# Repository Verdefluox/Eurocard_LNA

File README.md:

# Eurocard_LNA
A general purpose AC/DC low noise preamplifier on Eurocard format PCB

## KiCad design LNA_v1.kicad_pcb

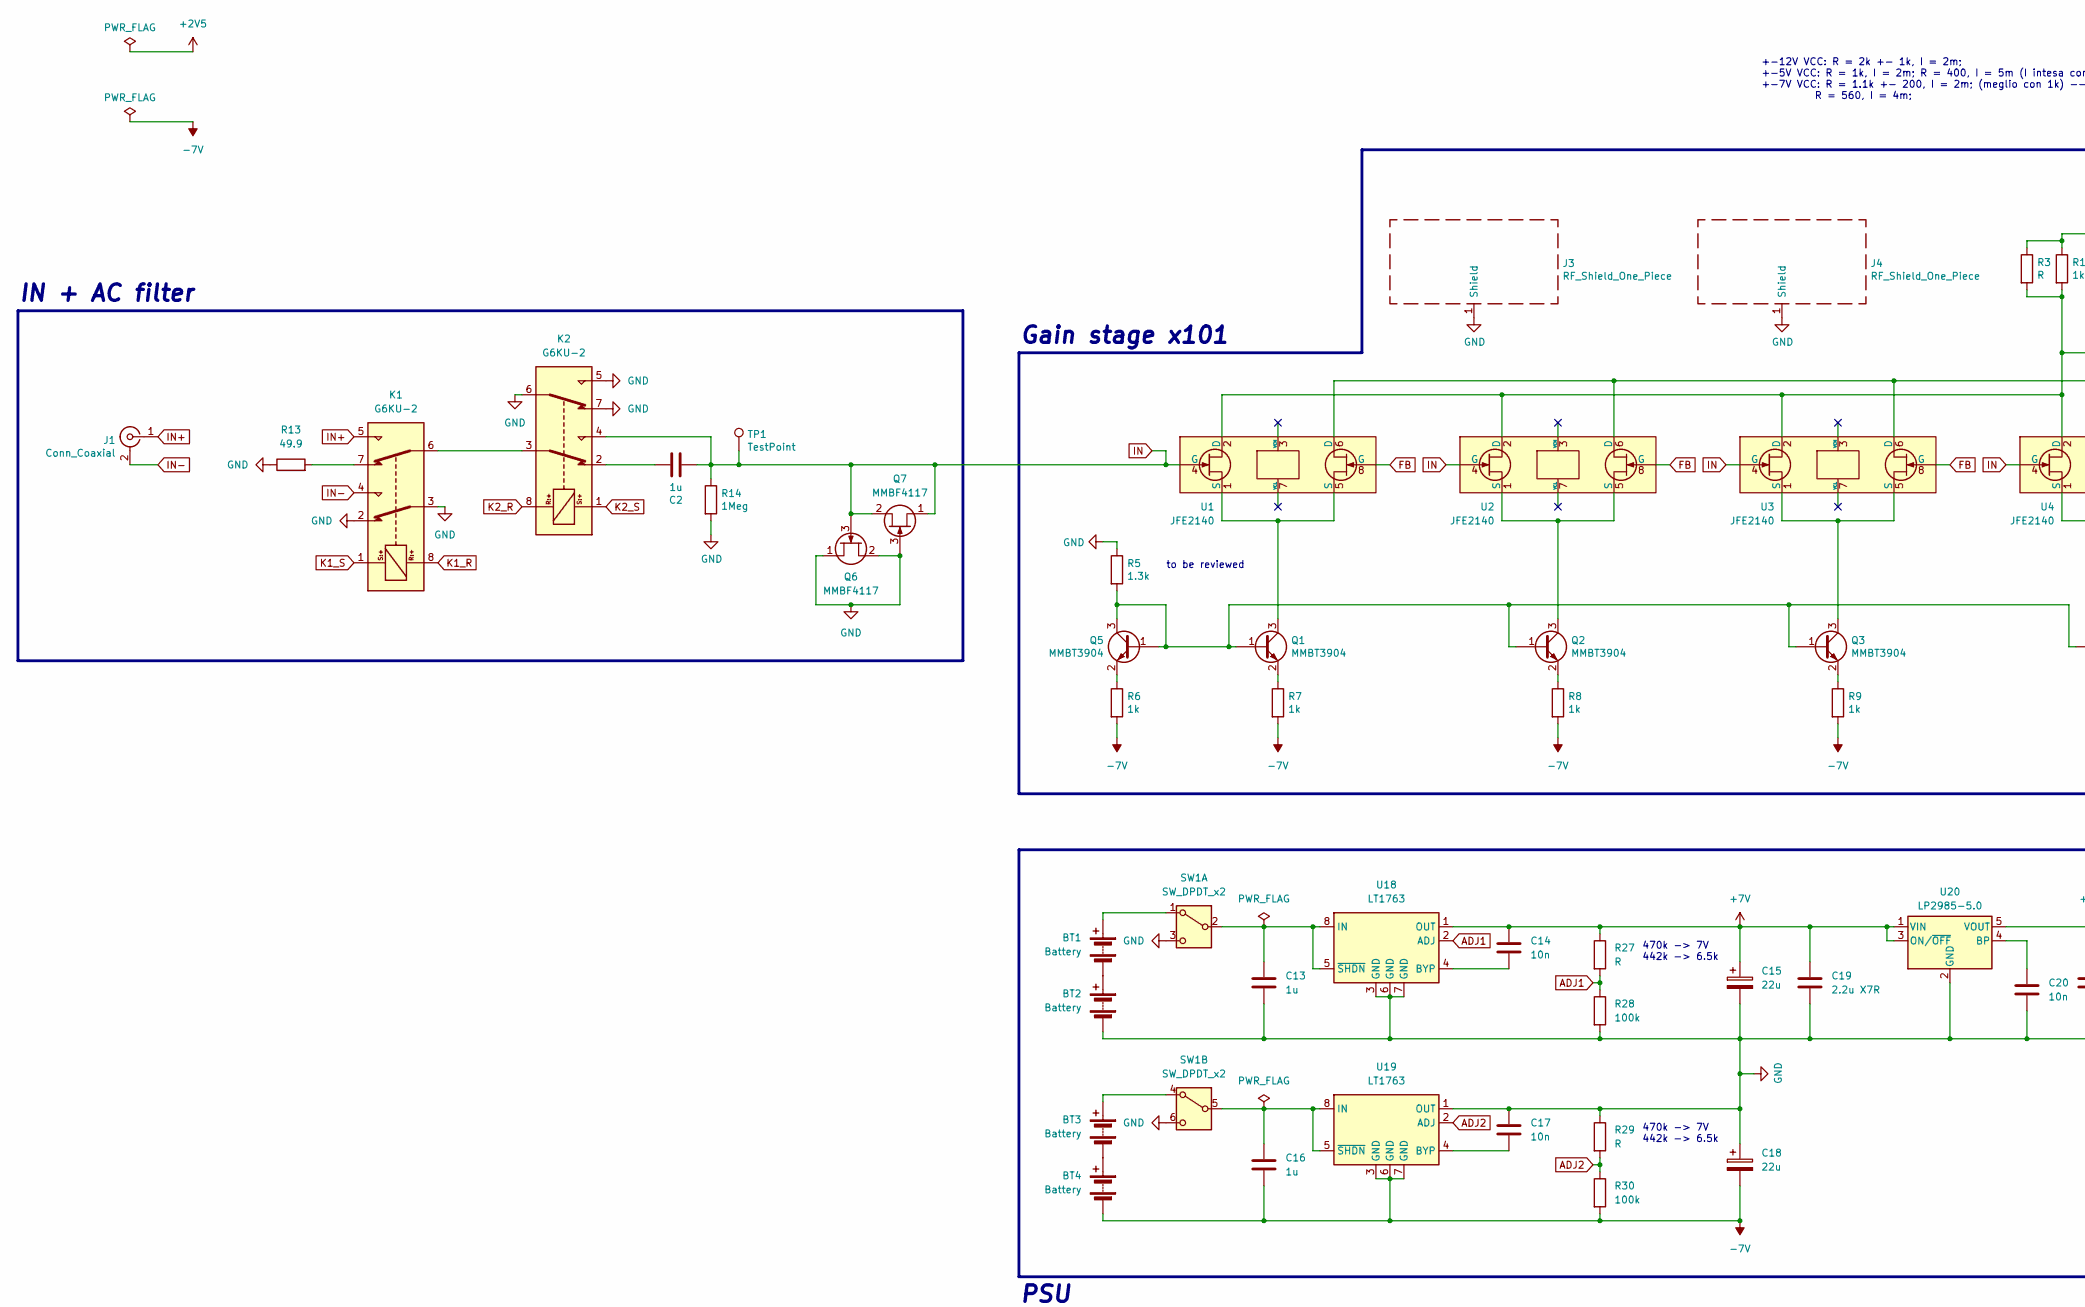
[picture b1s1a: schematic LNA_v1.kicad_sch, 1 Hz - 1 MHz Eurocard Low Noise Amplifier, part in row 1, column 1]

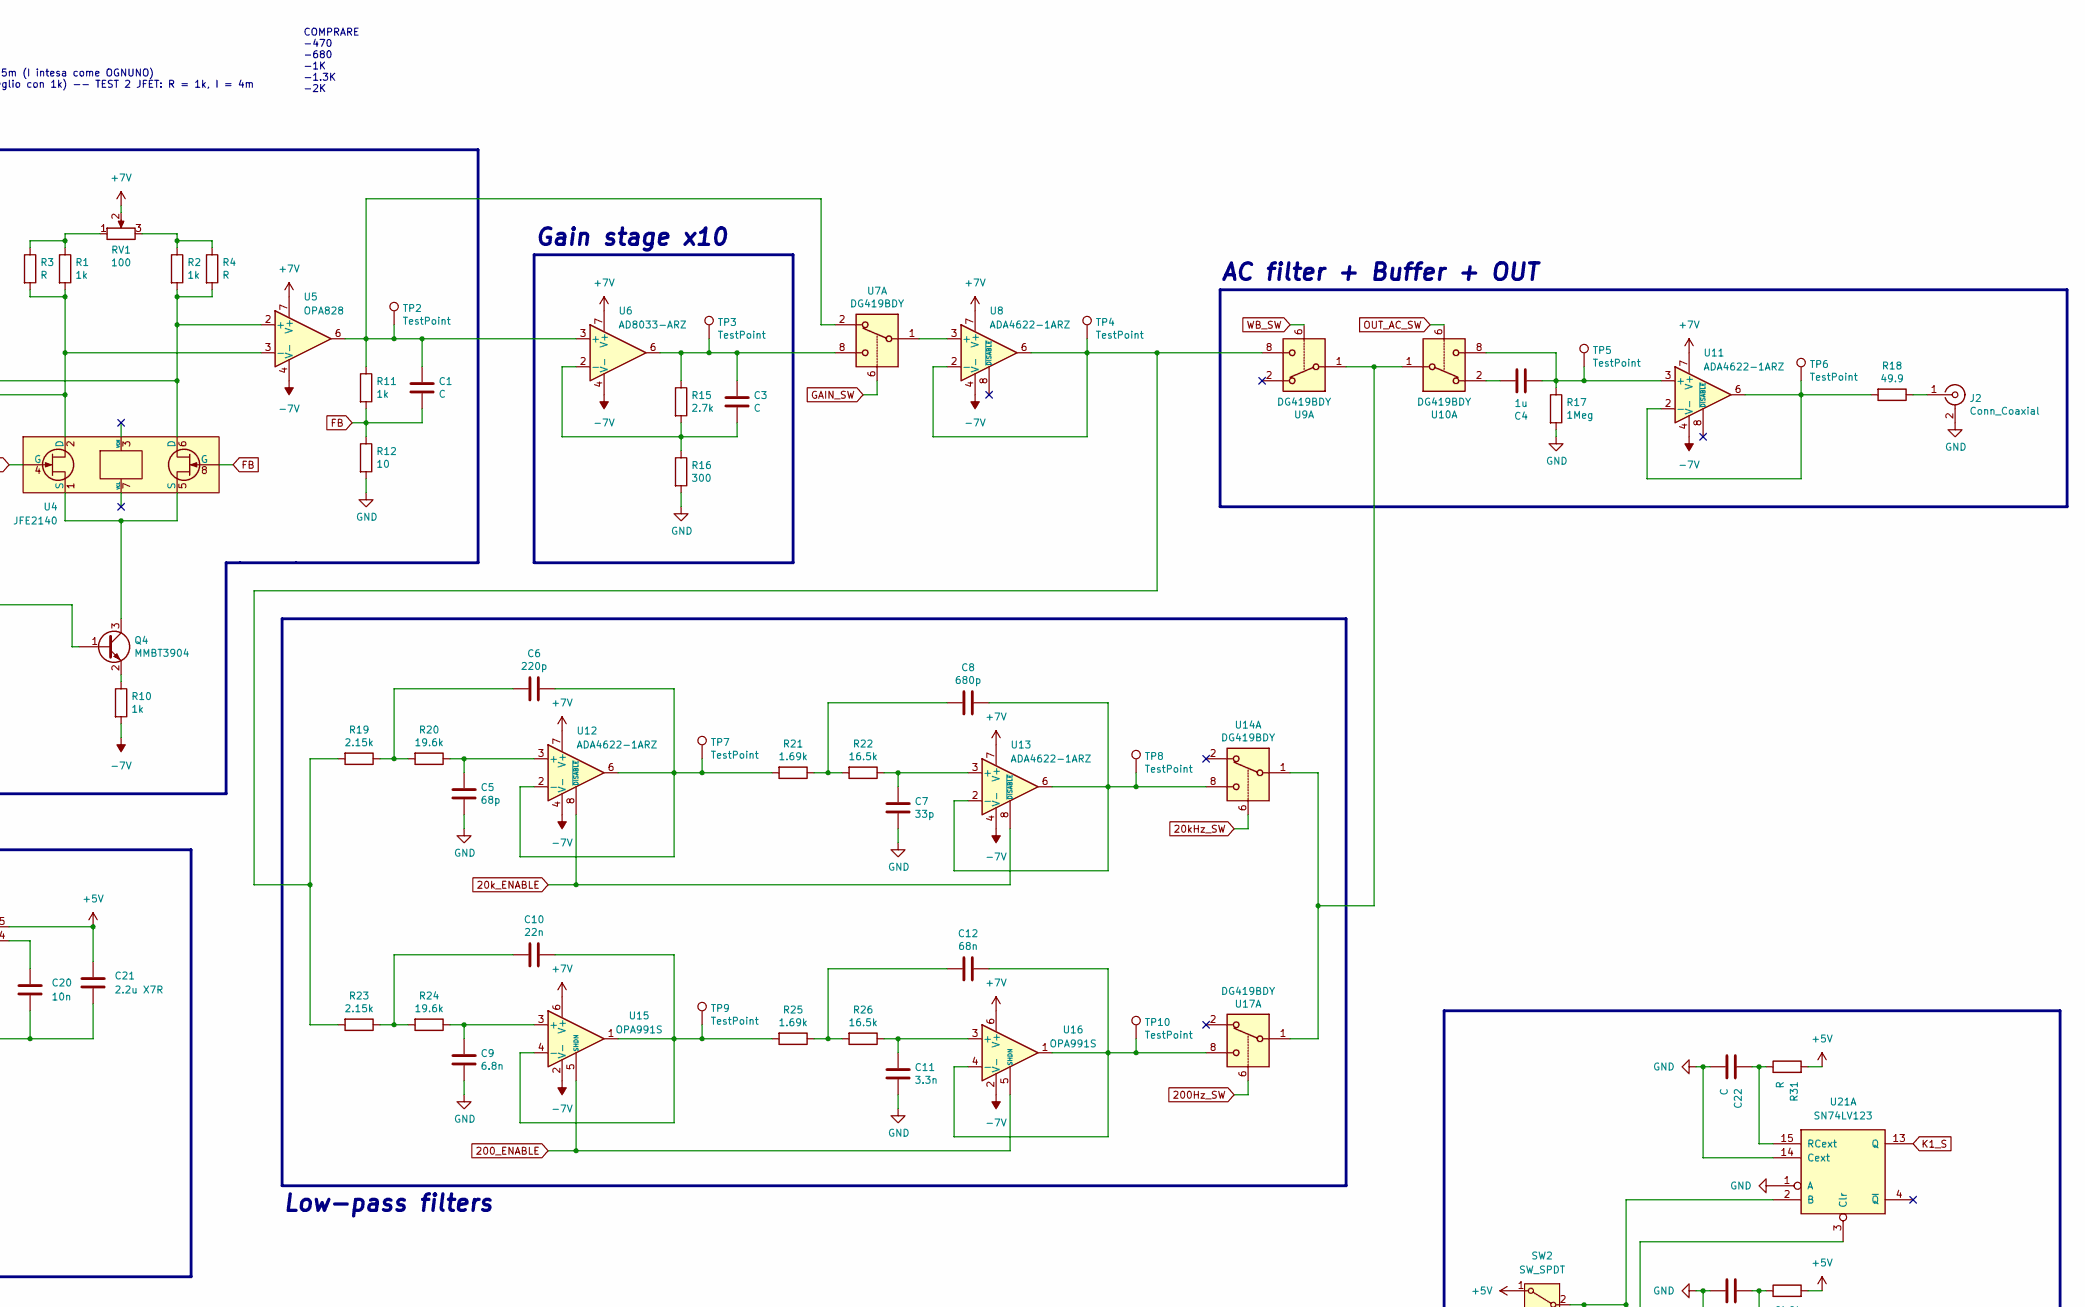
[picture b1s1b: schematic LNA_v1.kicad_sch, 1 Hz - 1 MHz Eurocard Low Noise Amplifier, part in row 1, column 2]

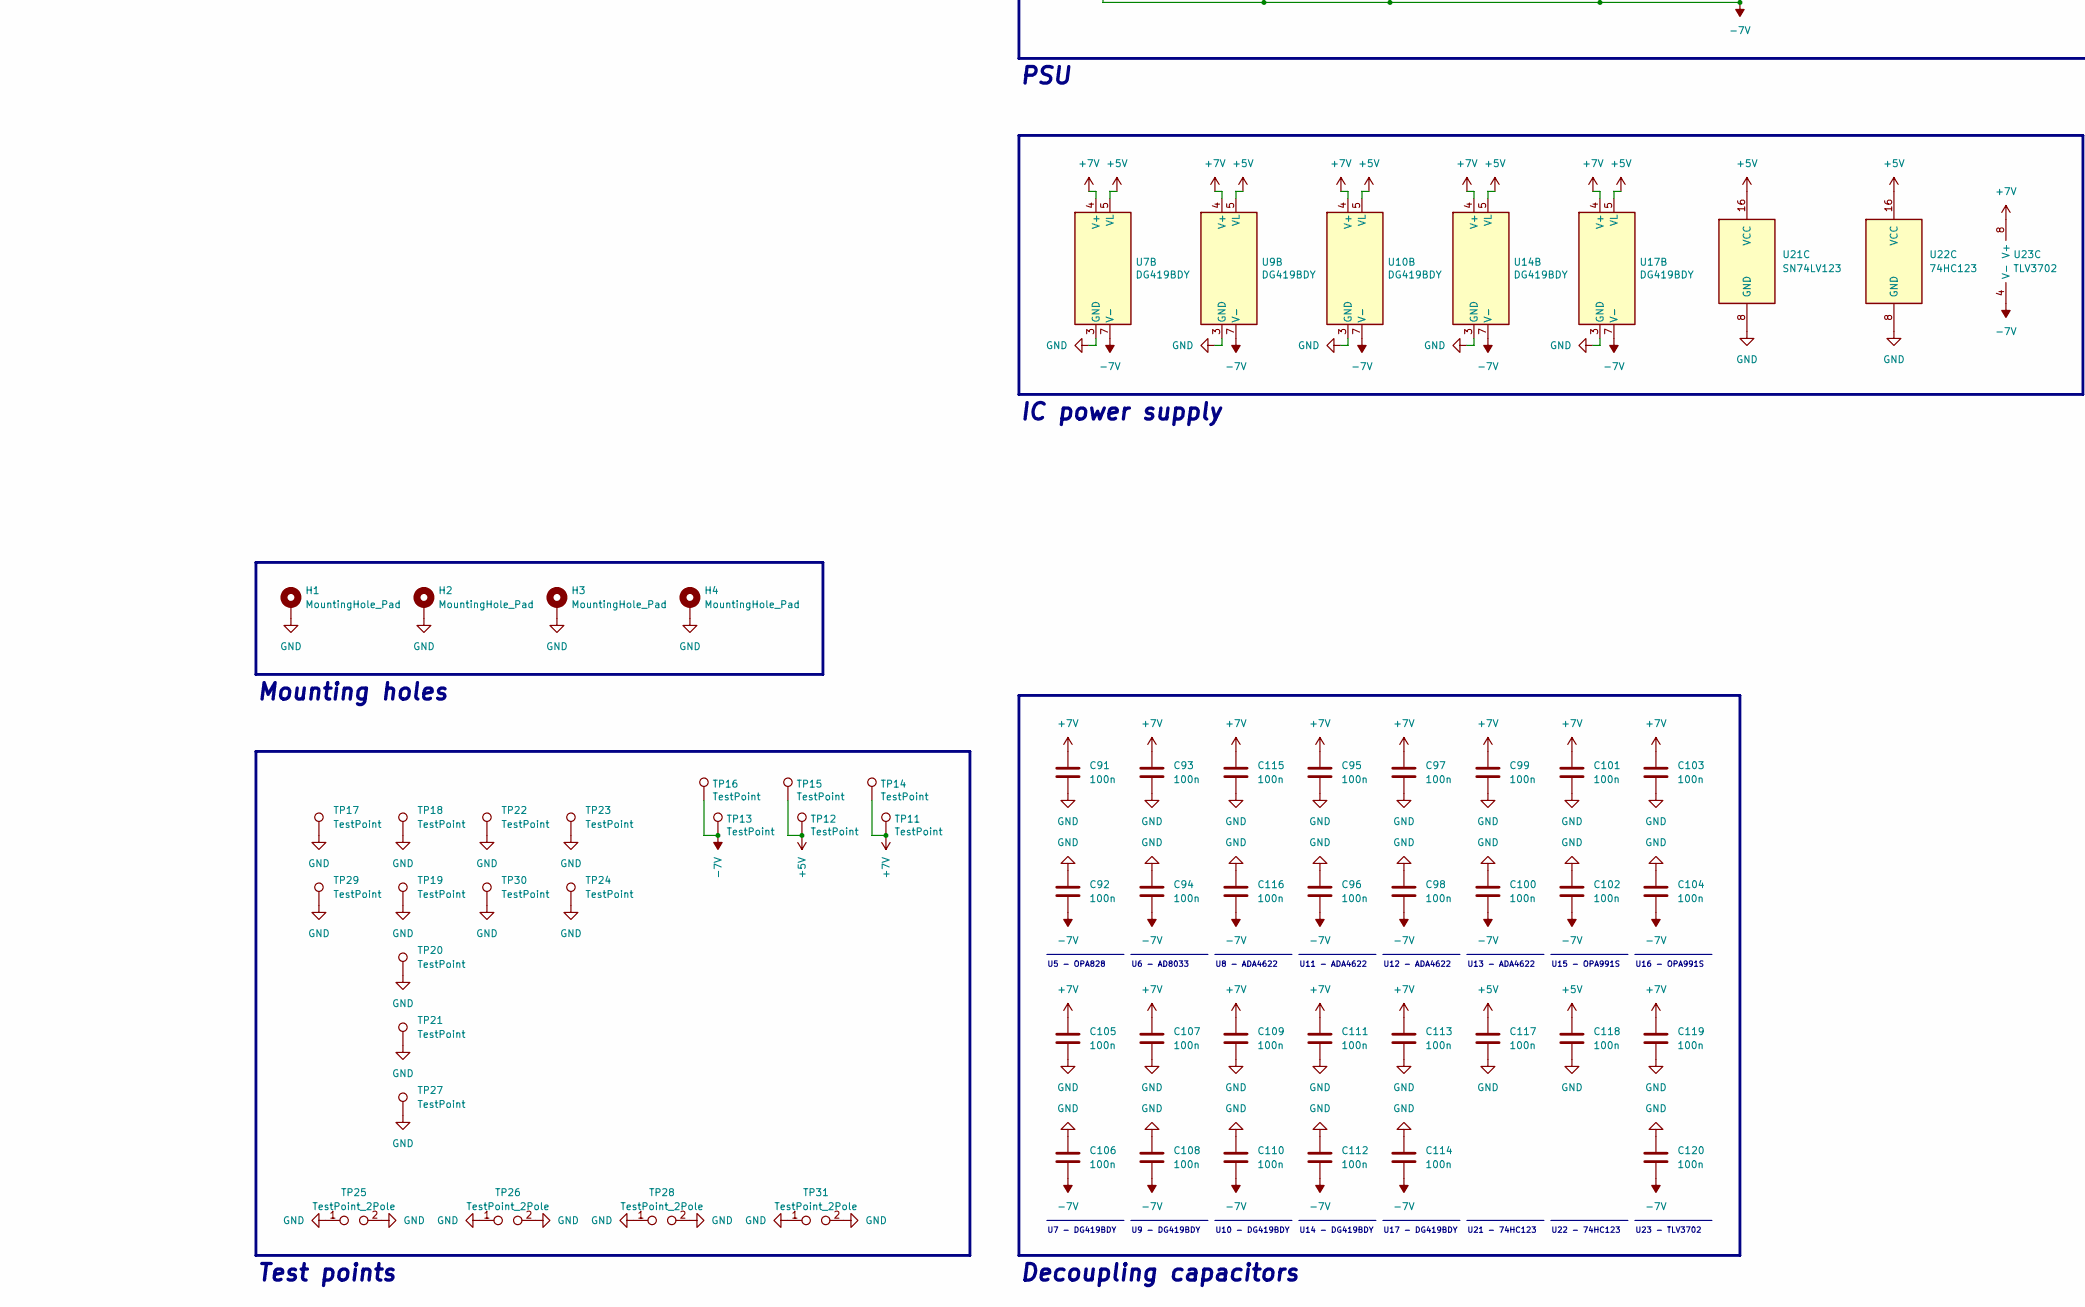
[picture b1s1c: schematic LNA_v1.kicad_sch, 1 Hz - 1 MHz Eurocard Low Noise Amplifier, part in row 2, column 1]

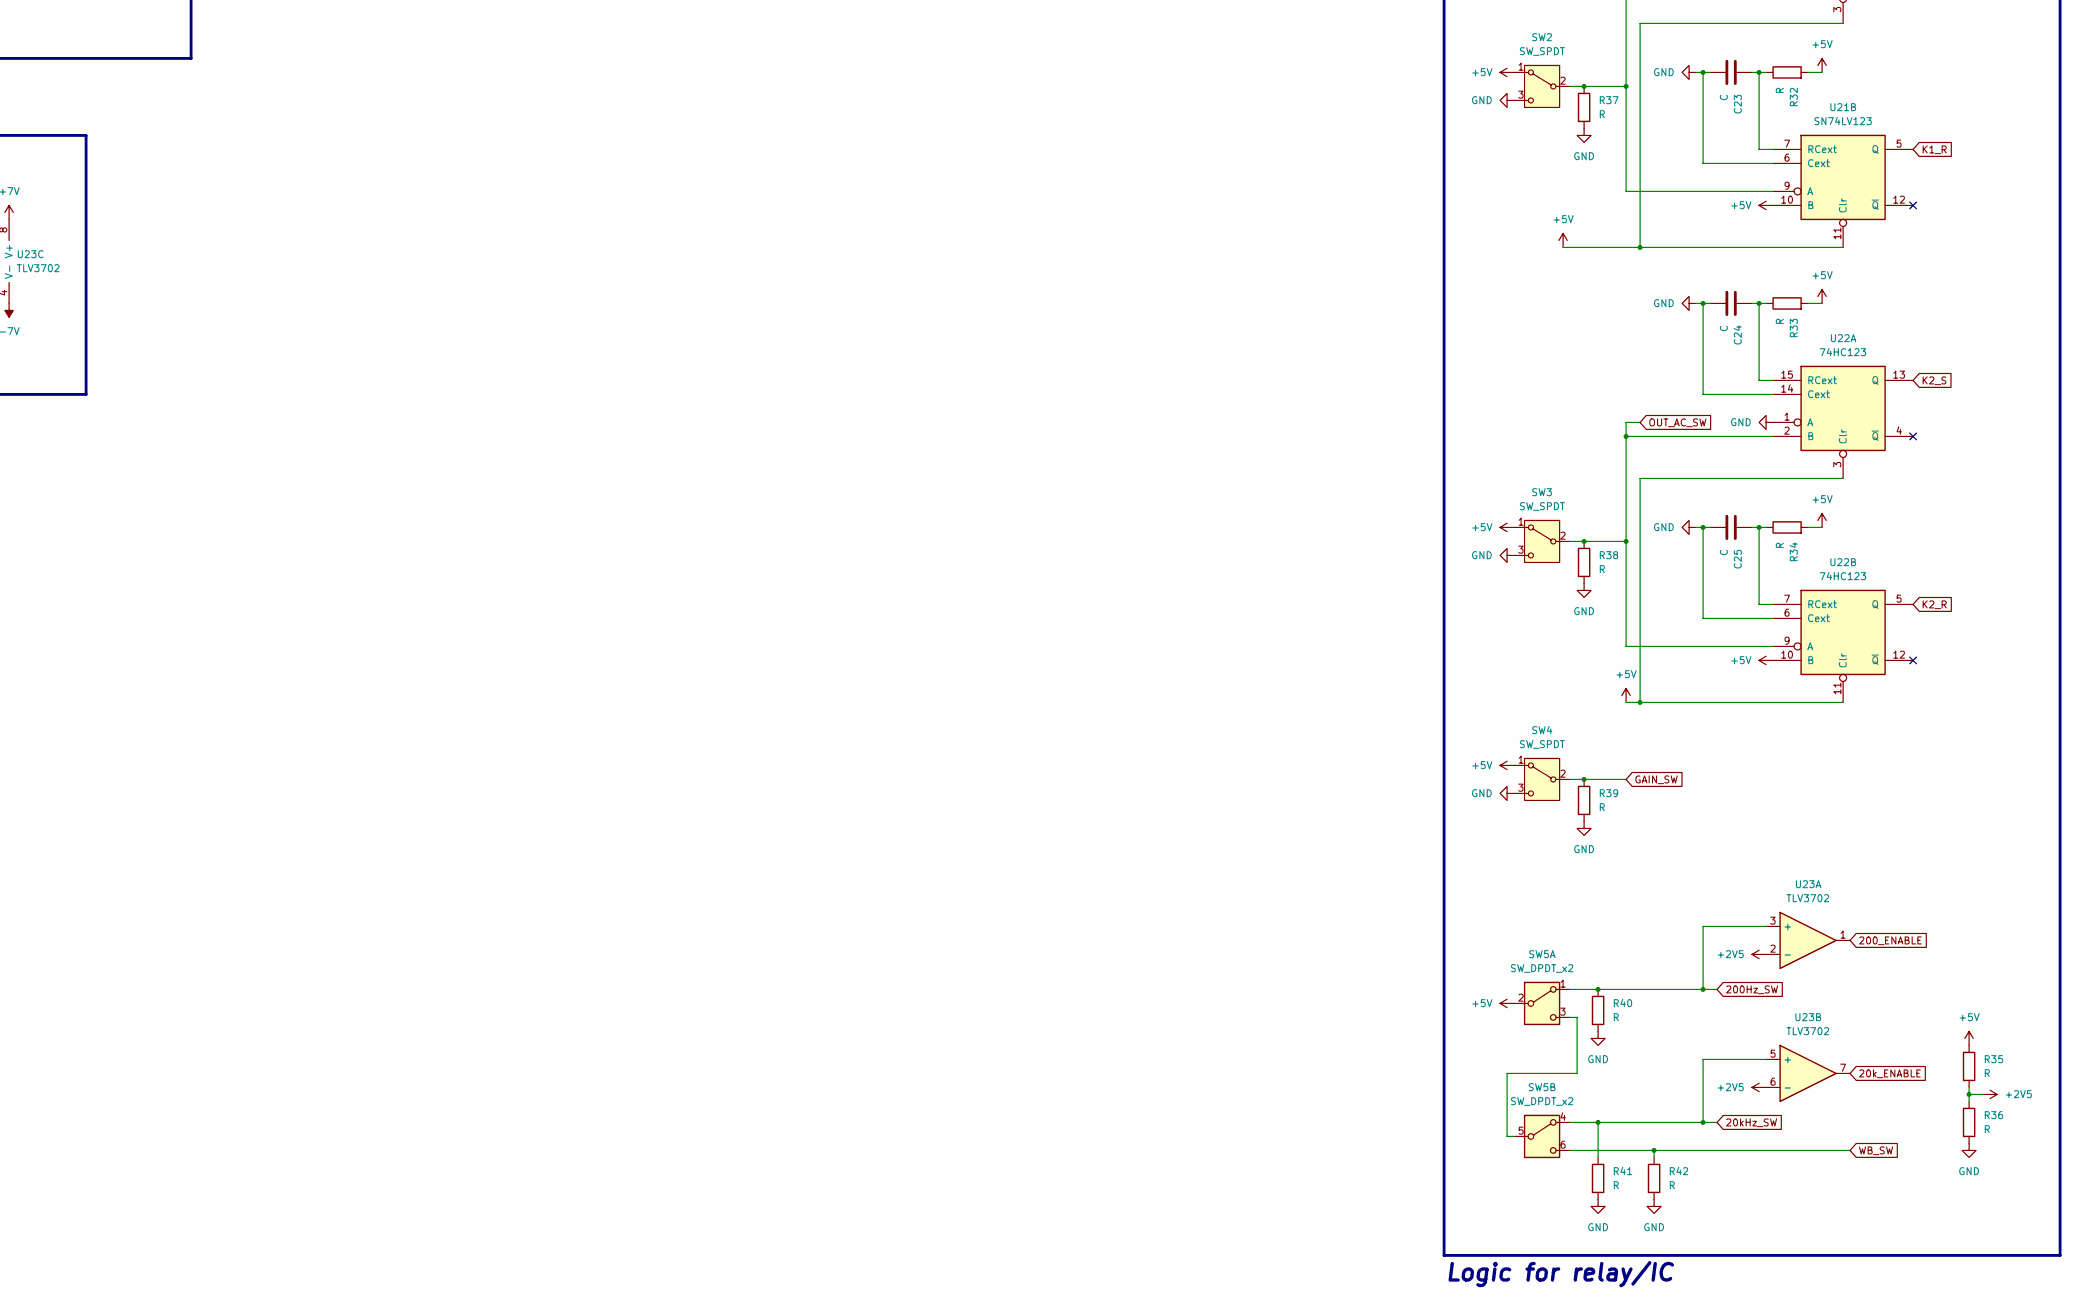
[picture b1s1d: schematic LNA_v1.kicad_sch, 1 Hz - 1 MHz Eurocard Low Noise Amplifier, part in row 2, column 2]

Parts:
BT1, BT2, BT3, BT4: Battery; 14500_Keystone53
C1, C3: C; C_0805_2012Metric_Pad1.18x1.45mm_HandSolder
C2, C4: 1u; C_Rect_L16.5mm_W7.3mm_P15.00mm_MKT
C5: 68p; C_1206_3216Metric_Pad1.33x1.80mm_HandSolder
C6: 220p; C_1206_3216Metric_Pad1.33x1.80mm_HandSolder
C7: 33p; C_1206_3216Metric_Pad1.33x1.80mm_HandSolder
C8: 680p; C_1206_3216Metric_Pad1.33x1.80mm_HandSolder
C9: 6.8n; C_1206_3216Metric_Pad1.33x1.80mm_HandSolder
C10: 22n; C_1206_3216Metric_Pad1.33x1.80mm_HandSolder
C11: 3.3n; C_1206_3216Metric_Pad1.33x1.80mm_HandSolder
C12: 68n; C_1206_3216Metric_Pad1.33x1.80mm_HandSolder
C13, C16: 1u; C_1206_3216Metric_Pad1.33x1.80mm_HandSolder
C14, C17: 10n; C_0805_2012Metric_Pad1.18x1.45mm_HandSolder
C15, C18: 22u; CP_EIA-3528-21_Kemet-B_Pad1.50x2.35mm_HandSolder
C19, C21: 2.2u X7R; C_1206_3216Metric_Pad1.33x1.80mm_HandSolder
C20: 10n; C_1206_3216Metric_Pad1.33x1.80mm_HandSolder
C22, C23, C24, C25: C; C_1206_3216Metric_Pad1.33x1.80mm_HandSolder
C91, C92, C93, C94, C95, C96, C97, C98, C99, C100, C101, C102, C103, C104, C105, C106, C107, C108, C109, C110, C111, C112, C113, C114, C115, C116, C117, C118, C119, C120: 100n; C_1206_3216Metric_Pad1.33x1.80mm_HandSolder
H1, H2, H3, H4: MountingHole_Pad; MountingHole_2.2mm_M2_Pad_Via
J1, J2: Conn_Coaxial; BNC_Amphenol_B6252HB-NPP3G-50_Horizontal
J3, J4: RF_Shield_One_Piece; Wuerth_36103305_30x30mm
K1, K2: G6KU-2; Relay_DPDT_Omron_G6K-2F-Y
Q1, Q2, Q3, Q4, Q5: MMBT3904; SOT-23W
Q6, Q7: MMBF4117; SOT-23
R1, R2, R6, R7, R8, R9, R10, R11: 1k; R_1206_3216Metric_Pad1.30x1.75mm_HandSolder
R3, R4, R31, R32, R33, R34, R35, R36, R37, R38, R39, R40, R41, R42: R; R_1206_3216Metric_Pad1.30x1.75mm_HandSolder
R5: 1.3k; R_1206_3216Metric_Pad1.30x1.75mm_HandSolder
R12: 10; R_1206_3216Metric_Pad1.30x1.75mm_HandSolder
R13, R18: 49.9; R_1206_3216Metric_Pad1.30x1.75mm_HandSolder
R14, R17: 1Meg; R_1206_3216Metric_Pad1.30x1.75mm_HandSolder
R15: 2.7k; R_1206_3216Metric_Pad1.30x1.75mm_HandSolder
R16: 300; R_1206_3216Metric_Pad1.30x1.75mm_HandSolder
R19, R23: 2.15k; R_1206_3216Metric_Pad1.30x1.75mm_HandSolder
R20, R24: 19.6k; R_1206_3216Metric_Pad1.30x1.75mm_HandSolder
R21, R25: 1.69k; R_1206_3216Metric_Pad1.30x1.75mm_HandSolder
R22, R26: 16.5k; R_1206_3216Metric_Pad1.30x1.75mm_HandSolder
R27, R29: R; R_0805_2012Metric_Pad1.20x1.40mm_HandSolder
R28, R30: 100k; R_0805_2012Metric_Pad1.20x1.40mm_HandSolder
RV1: 100; Potentiometer_Bourns_3296W_Vertical
SW1, SW5: SW_DPDT_x2; 100DPXTXBXMXXX
SW2, SW3, SW4: SW_SPDT; 100AWSPXTXBXMXXX
TP1: TestPoint; TestPoint_Pad_D1.5mm
TP2, TP3, TP4, TP5, TP6, TP7, TP8, TP9, TP10, TP11, TP12, TP13, TP14, TP15, TP16: TestPoint; TestPoint_Pad_D1.0mm
TP17, TP18, TP19, TP20, TP21, TP22, TP23, TP24, TP27, TP29, TP30: TestPoint; TestPoint_THTPad_D1.0mm_Drill0.5mm
TP25, TP26, TP28, TP31: TestPoint_2Pole; TestPoint_2Pads_Pitch5.08mm_Drill1.3mm
U1, U2, U3, U4: JFE2140; SOIC-8_3.9x4.9mm_P1.27mm
U5: OPA828; SOIC-8_3.9x4.9mm_P1.27mm
U6: AD8033-ARZ; SOIC-8_3.9x4.9mm_P1.27mm
U7, U9, U10, U14, U17: DG419BDY; SOIC-8_3.9x4.9mm_P1.27mm
U8, U11, U12, U13: ADA4622-1ARZ; SOIC-8_3.9x4.9mm_P1.27mm
U15, U16: OPA991S; SOT-23-6
U18, U19: LT1763; SOIC-8_3.9x4.9mm_P1.27mm
U20: LP2985-5.0; SOT-23-5
U21: SN74LV123; SOIC-16_3.9x9.9mm_P1.27mm
U22: 74HC123; SOIC-16_3.9x9.9mm_P1.27mm
U23: TLV3702; SOIC-8_3.9x4.9mm_P1.27mm

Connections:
20kHz_SW: R41.1, SW5.4 (A), U14.6, U23.5 (+)
20k_ENABLE: U12.8 (~DISABLE), U13.8 (~DISABLE), U23.7
200Hz_SW: R40.1, SW5.1 (A), U17.6, U23.3 (+)
200_ENABLE: U15.5 (SHDN), U16.5 (SHDN), U23.1
+2V5: R35.2, R36.1, U23.2 (-), U23.6 (-)
+5V: C21.1, C117.1, C118.1, R31.2, R32.2, R33.2, R34.2, R35.1, SW2.1 (A), SW3.1 (A), SW4.1 (A), SW5.2 (B), TP12.1, TP15.1, U7.5 (VL), U9.5 (VL), U10.5 (VL), U14.5 (VL), U17.5 (VL), U20.5 (VOUT), U21.3 (Clr), U21.10 (B), U21.11 (Clr), U21.16 (VCC), U22.3 (Clr), U22.10 (B), U22.11 (Clr), U22.16 (VCC)
+7V: C14.1, C15.1, C19.1, C91.1, C93.1, C95.1, C97.1, C99.1, C101.1, C103.1, C105.1, C107.1, C109.1, C111.1, C113.1, C115.1, C119.1, R27.1, RV1.2, TP11.1, TP14.1, U5.7 (V+), U6.7 (V+), U7.4 (V+), U8.7 (V+), U9.4 (V+), U10.4 (V+), U11.7 (V+), U12.7 (V+), U13.7 (V+), U14.4 (V+), U15.6 (V+), U16.6 (V+), U17.4 (V+), U18.1 (OUT), U20.1 (VIN), U20.3 (ON/~OFF), U23.8 (V+)
-7V: BT4.2 (-), C16.2, C18.2, C92.2, C94.2, C96.2, C98.2, C100.2, C102.2, C104.2, C106.2, C108.2, C110.2, C112.2, C114.2, C116.2, C120.2, R6.2, R7.2, R8.2, R9.2, R10.2, R30.2, TP13.1, TP16.1, U5.4 (V-), U6.4 (V-), U7.7 (V-), U8.4 (V-), U9.7 (V-), U10.7 (V-), U11.4 (V-), U12.4 (V-), U13.4 (V-), U14.7 (V-), U15.2 (V-), U16.2 (V-), U17.7 (V-), U19.3 (GND), U19.6 (GND), U19.7 (GND), U23.4 (V-)
ADJ1: R27.2, R28.1, U18.2 (ADJ)
ADJ2: R29.2, R30.1, U19.2 (ADJ)
FB: C1.2, R11.2, R12.1, U1.8 (G), U2.8 (G), U3.8 (G), U4.8 (G)
GAIN_SW: R39.1, SW4.2 (B), U7.6
GND: BT2.2 (-), C5.1, C7.1, C9.1, C11.1, C13.2, C15.2, C17.1, C18.1, C19.2, C20.2, C21.2, C22.2, C23.2, C24.2, C25.2, C91.2, C92.1, C93.2, C94.1, C95.2, C96.1, C97.2, C98.1, C99.2, C100.1, C101.2, C102.1, C103.2, C104.1, C105.2, C106.1, C107.2, C108.1, C109.2, C110.1, C111.2, C112.1, C113.2, C114.1, C115.2, C116.1, C117.2, C118.2, C119.2, C120.1, H1.1, H2.1, H3.1, H4.1, J2.2 (Ext), J3.1 (Shield), J4.1 (Shield), K1.2, K1.3, K2.5, K2.6, K2.7, Q6.1 (S), Q6.2 (D), Q7.3 (G), R5.1, R12.2, R13.1, R14.2, R16.2, R17.2, R28.2, R29.1, R36.2, R37.2, R38.2, R39.2, R40.2, R41.2, R42.2, SW1.3 (C), SW1.6 (C), SW2.3 (C), SW3.3 (C), SW4.3 (C), TP17.1, TP18.1, TP19.1, TP20.1, TP21.1, TP22.1, TP23.1, TP24.1, TP25.1, TP25.2, TP26.1, TP26.2, TP27.1, TP28.1, TP28.2, TP29.1, TP30.1, TP31.1, TP31.2, U7.3 (GND), U9.3 (GND), U10.3 (GND), U14.3 (GND), U17.3 (GND), U18.3 (GND), U18.6 (GND), U18.7 (GND), U19.1 (OUT), U20.2 (GND), U21.1 (A), U21.6 (Cext), U21.8 (GND), U21.14 (Cext), U22.1 (A), U22.6 (Cext), U22.8 (GND), U22.14 (Cext)
IN: C2.1, K2.4, Q6.3 (G), Q7.1 (S), Q7.2 (D), R14.1, TP1.1, U1.4 (G), U2.4 (G), U3.4 (G), U4.4 (G)
IN+: J1.1 (In), K1.5
IN-: J1.2 (Ext), K1.4
K1_R: K1.8, U21.5 (Q)
K1_S: K1.1, U21.13 (Q)
K2_R: K2.8, U22.5 (Q)
K2_S: K2.1, U22.13 (Q)
unnamed: BT1.1 (+), SW1.1 (A)
unnamed: BT1.2 (-), BT2.1 (+)
unnamed: BT3.1 (+), SW1.4 (A)
unnamed: BT3.2 (-), BT4.1 (+)
unnamed: C2.2, K2.2
unnamed: C3.1, R15.1, TP3.1, U6.6, U7.8
unnamed: C4.2, U10.2
unnamed: C6.2, R19.1, R20.2
unnamed: C8.2, R21.1, R22.2
unnamed: C10.2, R23.1, R24.2
unnamed: C12.2, R25.1, R26.2
unnamed: J2.1 (In), R18.1
unnamed: K1.6, K2.3
unnamed: K1.7, R13.2
unnamed: Q1.1 (B), Q2.1 (B), Q3.1 (B), Q4.1 (B), Q5.1 (B), Q5.3 (C), R5.2
unnamed: Q1.3 (C), U1.1 (S), U1.5 (S)
unnamed: Q1.2 (E), R7.1
unnamed: Q2.3 (C), U2.1 (S), U2.5 (S)
unnamed: Q2.2 (E), R8.1
unnamed: Q3.3 (C), U3.1 (S), U3.5 (S)
unnamed: Q3.2 (E), R9.1
unnamed: Q4.3 (C), U4.1 (S), U4.5 (S)
unnamed: Q4.2 (E), R10.1
unnamed: Q5.2 (E), R6.1
unnamed: R1.1, R3.1, RV1.1
unnamed: R2.1, R4.1, RV1.3
unnamed: C13.1, SW1.2 (B), U18.5 (~SHDN), U18.8 (IN)
unnamed: C16.1, SW1.5 (B), U19.5 (~SHDN), U19.8 (IN)
unnamed: R37.1, SW2.2 (B), U21.2 (B), U21.9 (A)
unnamed: SW5.3 (C), SW5.5 (B)
unnamed: R2.2, R4.2, U1.6 (D), U2.6 (D), U3.6 (D), U4.6 (D), U5.2 (+)
unnamed: R1.2, R3.2, U1.2 (D), U2.2 (D), U3.2 (D), U4.2 (D), U5.3 (-)
unnamed: C1.1, R11.1, TP2.1, U5.6, U6.3 (+), U7.2
unnamed: C3.2, R15.2, R16.1, U6.2 (-)
unnamed: U7.1, U8.3 (+)
unnamed: R19.2, R23.2, TP4.1, U8.2 (-), U8.6, U9.8
unnamed: U9.1, U10.1, U14.1, U17.1
unnamed: C4.1, R17.1, TP5.1, U10.8, U11.3 (+)
unnamed: R18.2, TP6.1, U11.2 (-), U11.6
unnamed: C5.2, R20.1, U12.3 (+)
unnamed: C6.1, R21.2, TP7.1, U12.2 (-), U12.6
unnamed: C7.2, R22.1, U13.3 (+)
unnamed: C8.1, TP8.1, U13.2 (-), U13.6, U14.8
unnamed: C9.2, R24.1, U15.3 (+)
unnamed: C10.1, R25.2, TP9.1, U15.1, U15.4 (-)
unnamed: C11.2, R26.1, U16.3 (+)
unnamed: C12.1, TP10.1, U16.1, U16.4 (-), U17.8
unnamed: C14.2, U18.4 (BYP)
unnamed: C17.2, U19.4 (BYP)
unnamed: C20.1, U20.4 (BP)
unnamed: C22.1, R31.1, U21.15 (RCext)
unnamed: C23.1, R32.1, U21.7 (RCext)
unnamed: C24.1, R33.1, U22.15 (RCext)
unnamed: C25.1, R34.1, U22.7 (RCext)
OUT_AC_SW: R38.1, SW3.2 (B), U10.6, U22.2 (B), U22.9 (A)
WB_SW: R42.1, SW5.6 (C), U9.6

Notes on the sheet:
U17 - DG419BDY
U21 - 74HC123
Logic for relay/IC
+-12V VCC: R = 2k +- 1k, I = 2m; +-5V VCC: R = 1k, I = 2m; R = 400, I = 5m (I intesa come OGNUNO) +-7V VCC: R = 1.1k +- 200, I = 2m; (meglio con 1k) -- TEST 2 JFET: R = 1k, I = 4m R = 560, I = 4m;
470k -> 7V 442k -> 6.5k
IN + AC filter
U6 - AD8033
U23 - TLV3702
Decoupling capacitors
U13 - ADA4622
U7 - DG419BDY
to be reviewed
U8 - ADA4622
U14 - DG419BDY
U16 - OPA991S
IC power supply
PSU
U5 - OPA828
Gain stage x101
U12 - ADA4622
AC filter + Buffer + OUT
Gain stage x10
U10 - DG419BDY
U15 - OPA991S
Low-pass filters
U22 - 74HC123
U9 - DG419BDY
COMPRARE -470 -680 -1K -1.3K -2K
Test points
Mounting holes
U11 - ADA4622

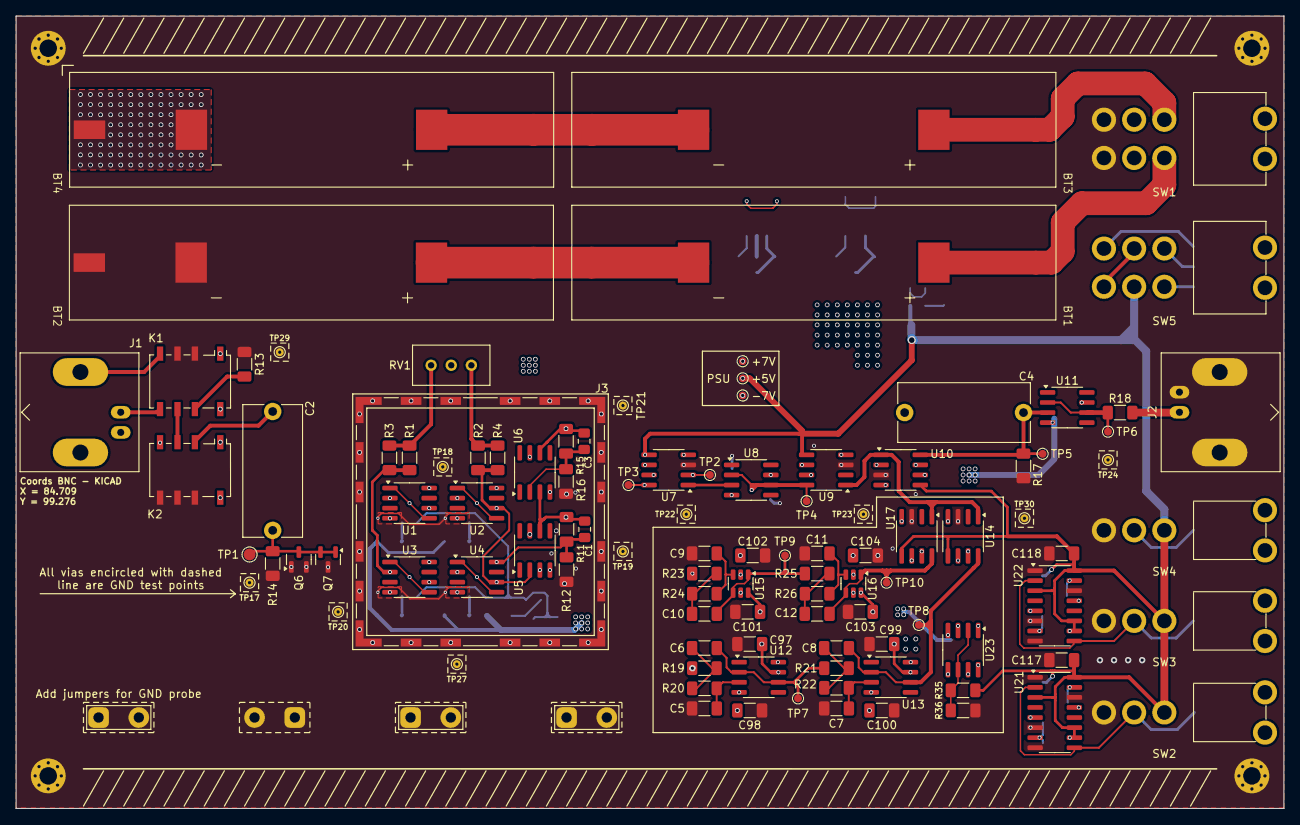
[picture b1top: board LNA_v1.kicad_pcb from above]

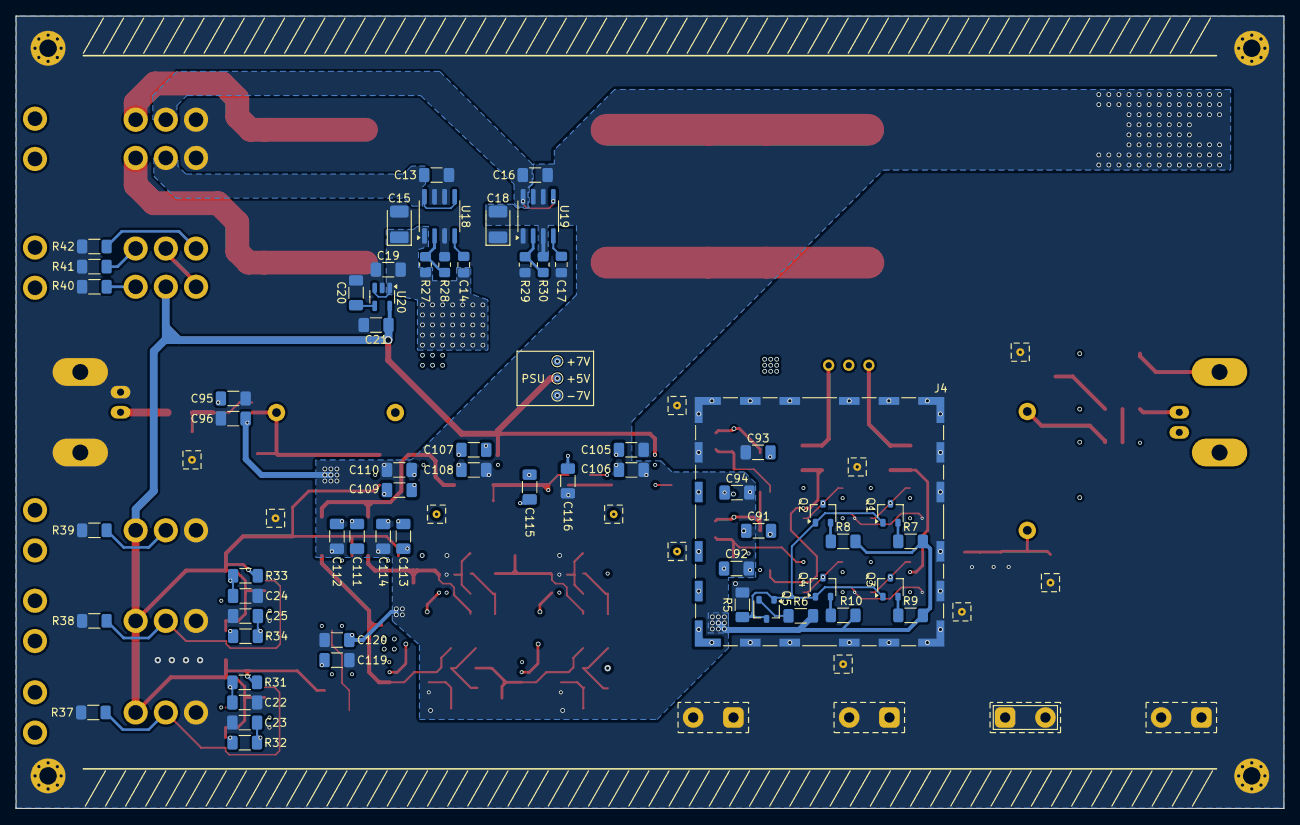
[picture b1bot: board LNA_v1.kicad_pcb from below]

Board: 4 copper layers, 160.0 x 100.0 mm, 178 parts (66 on the bottom side), 76 nets.
